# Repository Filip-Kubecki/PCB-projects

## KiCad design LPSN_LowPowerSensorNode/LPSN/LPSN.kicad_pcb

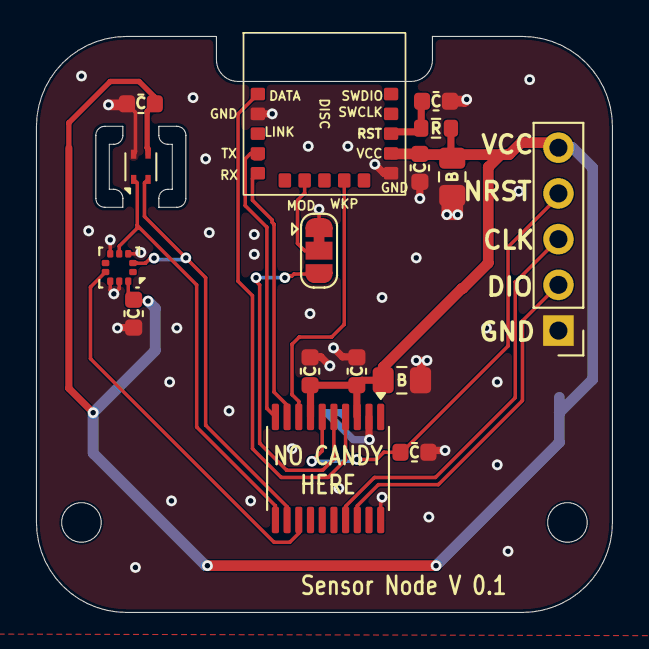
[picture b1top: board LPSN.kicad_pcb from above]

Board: 2 copper layers, 32.0 x 32.0 mm, 4 parts (1 on the bottom side), 5 nets.

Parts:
BT1: CR2032_cell; BatteryHolder_Multicomp_BC-2001_1x2032
U2: SHT4x; Sensirion_DFN-4_1.5x1.5mm_P0.8mm_SHT4x_NoCentralPad
U3: LPS22HB; ST_HLGA-10_2x2mm_P0.5mm_LayoutBorder3x2y
U5: STM32U031F6Px; TSSOP-20_4.4x6.5mm_P0.65mm

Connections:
GND: BT1.2 (-), U2.4 (VSS)
I2C_SCL: U2.2 (SCL), U3.2 (SCL), U5.12 (PA7/PB0)
I2C_SDA: U2.1 (SDA), U3.4 (SDA), U5.11 (PA5/PA6)
PRESS_INT_READY: U3.7 (INT_DRDY), U5.13 (PB1)
VCC: BT1.1 (+), U2.3 (VDD), U3.1 (Vdd_IO), U3.6 (~CS), U3.10 (VDD), U5.3 (VDD), U5.7 (VDDA)

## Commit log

2026-03-31 init commit
2026-03-31 Backup - System pomiaru ciśnienia
2026-03-31 LPSN - base for node PCB
2026-04-14 Ebyte_adapter
2026-04-21 Ebyte correct footprint
2026-04-28 LPSN - backup
2026-04-29 LPSN - backup backup
2026-05-03 LPSN - finalization of pcb
    PCB almost done. Needs review and double checking
2026-05-05 LPSN - production with gerber files v0.1
    Version that was send to JLCPCB
